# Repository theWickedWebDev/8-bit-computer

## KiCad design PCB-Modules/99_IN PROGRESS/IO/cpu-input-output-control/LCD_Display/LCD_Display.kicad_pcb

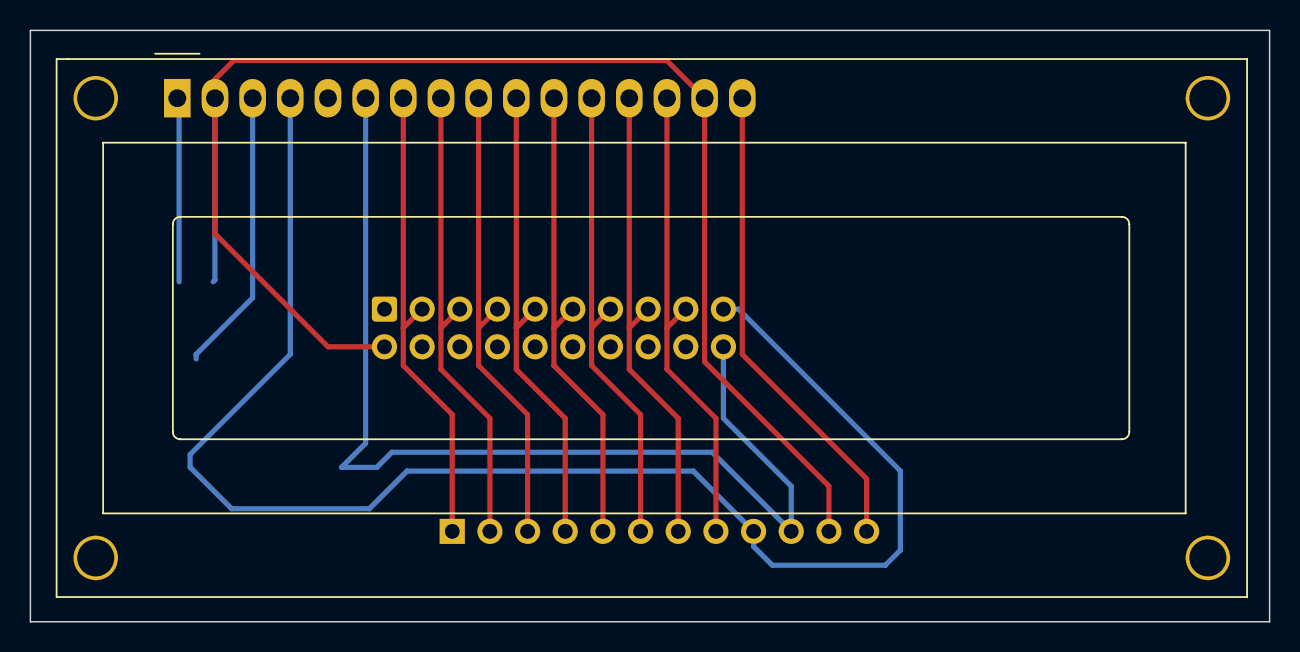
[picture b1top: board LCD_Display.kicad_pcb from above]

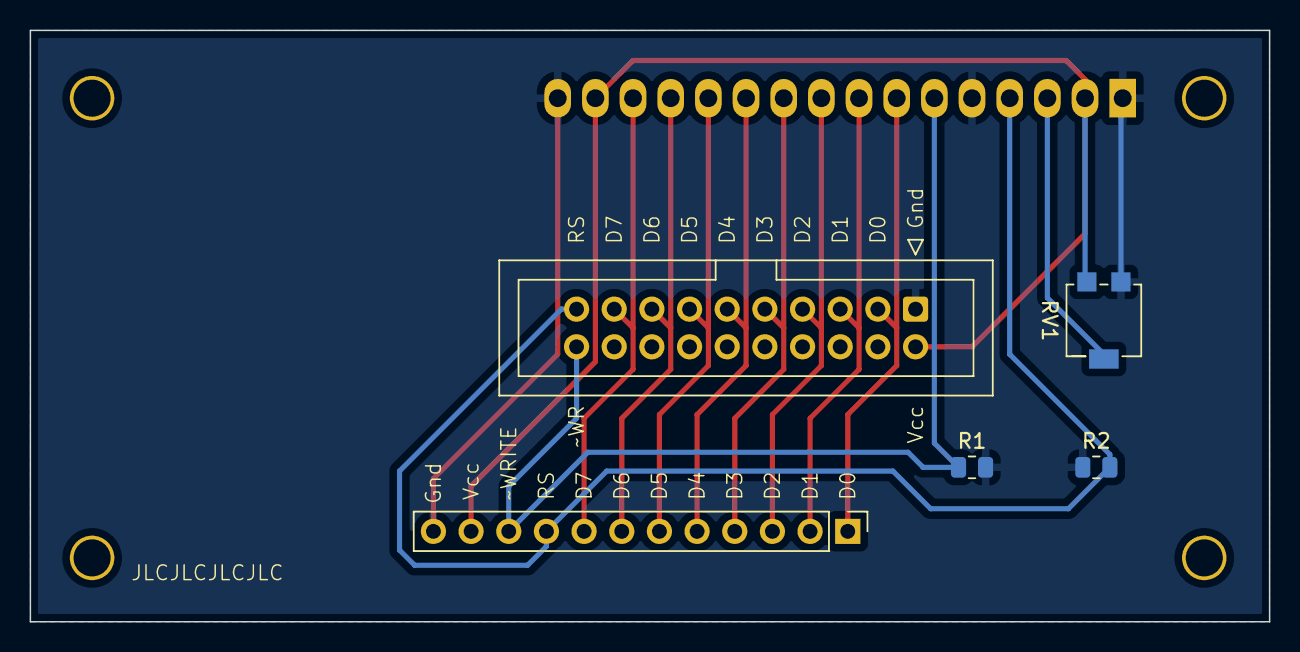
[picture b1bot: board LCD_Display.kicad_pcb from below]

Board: 2 copper layers, 83.6 x 39.9 mm, 6 parts (5 on the bottom side), 13 nets.

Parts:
DS1: WC1602A
J1: Conn_01x12; PinHeader_1x12_P2.54mm_Vertical
J21: Conn_02x20_Odd_Even; IDC-Header_2x10_P2.54mm_Vertical
R1, R2: R_Small_US; R_0805_2012Metric
RV1: R_Potentiometer_Trim_US; Potentiometer_Bourns_3224G_Horizontal

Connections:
/CONTRAST: DS1.3 (VO), RV1.2
/D0: DS1.7 (D0), J1.1, J21.3
/D1: DS1.8 (D1), J1.2, J21.5
/D2: DS1.9 (D2), J1.3, J21.7
/D3: DS1.10 (D3), J1.4, J21.9
/D4: DS1.11 (D4), J1.5, J21.11
/D5: DS1.12 (D5), J1.6, J21.13
/D6: DS1.13 (D6), J1.7, J21.15
/D7: DS1.14 (D7), J1.8, J21.17
/RS: DS1.4 (RS), J1.9, J21.19, R2.1
/~WRITE: DS1.6 (E), J1.10, J21.20, R1.1
GND: DS1.1 (VSS), DS1.5 (R/W), DS1.16 (LED(-)), J1.12, J21.1, R1.2, R2.2, RV1.3
VCC: DS1.2 (VDD), DS1.15 (LED(+)), J1.11, J21.2, RV1.1

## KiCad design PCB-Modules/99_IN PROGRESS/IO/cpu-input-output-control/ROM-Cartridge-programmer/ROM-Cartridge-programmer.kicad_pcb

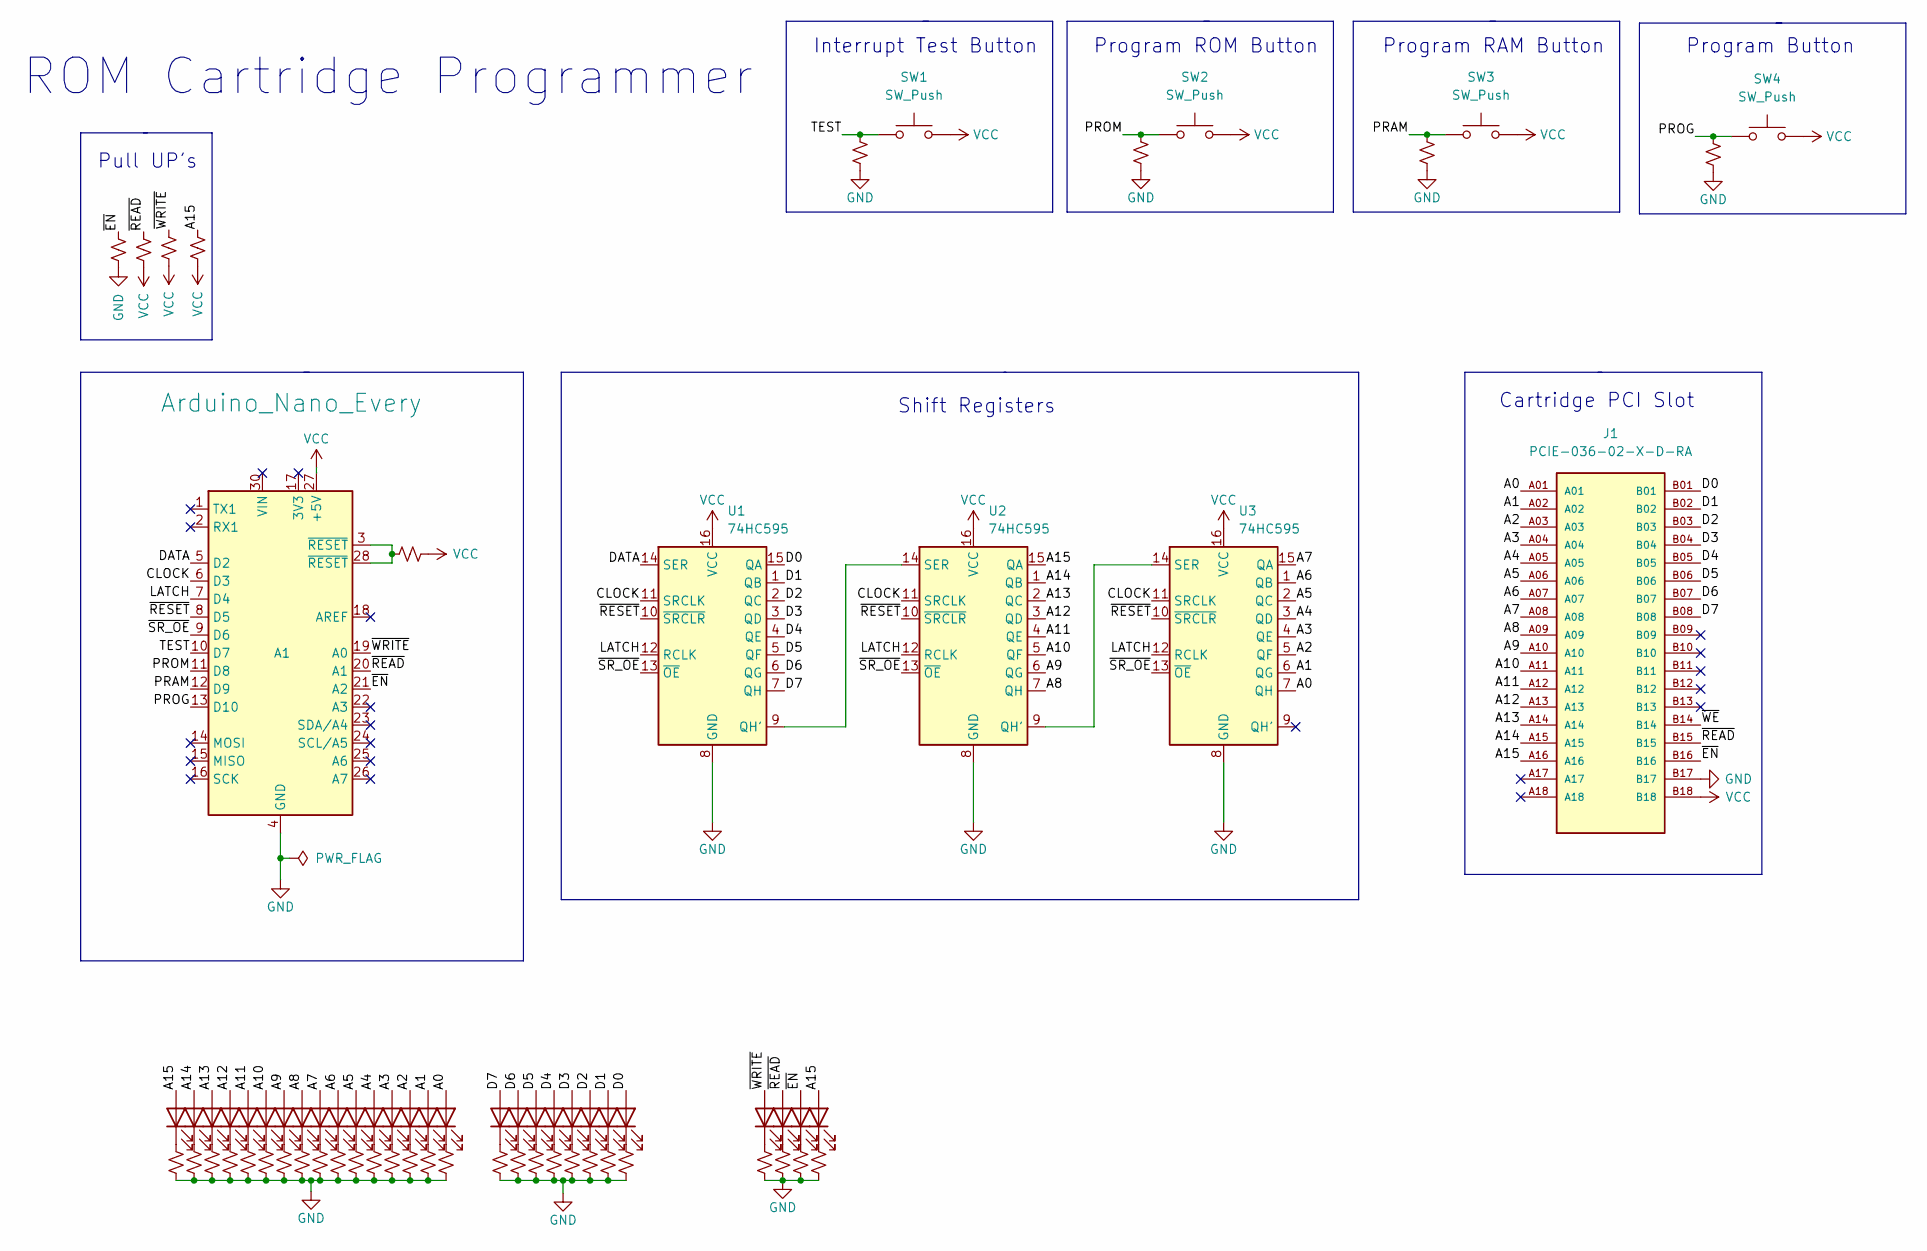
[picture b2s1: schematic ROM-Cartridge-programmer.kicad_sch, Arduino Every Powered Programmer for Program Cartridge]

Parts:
A1: Arduino_Nano_Every; Arduino_Nano
D1, D2, D3, D4, D5, D6, D7, D8, D9, D10, D11, D12, D13, D14, D15, D16, D17, D18, D19, D20, D21, D22, D23, D24, D25, D26, D27, D28: LED; LED_0805_2012Metric
J1: PCIE-036-02-X-D-RA; SAMTEC_PCIE-036-02-X-D-RA; PARTREV D
R1, R2, R3, R4, R5, R6, R7, R8, R9, R10, R11, R12, R13, R14, R15, R16, R17, R18, R19, R20, R21, R22, R23, R24, R25, R26, R27, R28, R29, R30, R31, R32, R33, R34, R35, R36, R37: R_Small_US; R_0805_2012Metric
SW1, SW2, SW3, SW4: SW_Push; SW_PUSH_6mm
U1, U2, U3: 74HC595; SOIC-16_3.9x9.9mm_P1.27mm

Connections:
/A0: D16.2 (A), J1.A01, U3.7 (QH)
/A1: D15.2 (A), J1.A02, U3.6 (QG)
/A2: D14.2 (A), J1.A03, U3.5 (QF)
/A3: D13.2 (A), J1.A04, U3.4 (QE)
/A4: D12.2 (A), J1.A05, U3.3 (QD)
/A5: D11.2 (A), J1.A06, U3.2 (QC)
/A6: D10.2 (A), J1.A07, U3.1 (QB)
/A7: D9.2 (A), J1.A08, U3.15 (QA)
/A8: D8.2 (A), J1.A09, U2.7 (QH)
/A9: D7.2 (A), J1.A10, U2.6 (QG)
/A10: D6.2 (A), J1.A11, U2.5 (QF)
/A11: D5.2 (A), J1.A12, U2.4 (QE)
/A12: D4.2 (A), J1.A13, U2.3 (QD)
/A13: D3.2 (A), J1.A14, U2.2 (QC)
/A14: D2.2 (A), J1.A15, U2.1 (QB)
/A15: D1.2 (A), D28.2 (A), J1.A16, R4.1, U2.15 (QA)
/CLOCK: A1.6 (D3), U1.11 (SRCLK), U2.11 (SRCLK), U3.11 (SRCLK)
/D0: D24.2 (A), J1.B01, U1.15 (QA)
/D1: D23.2 (A), J1.B02, U1.1 (QB)
/D2: D22.2 (A), J1.B03, U1.2 (QC)
/D3: D21.2 (A), J1.B04, U1.3 (QD)
/D4: D20.2 (A), J1.B05, U1.4 (QE)
/D5: D19.2 (A), J1.B06, U1.5 (QF)
/D6: D18.2 (A), J1.B07, U1.6 (QG)
/D7: D17.2 (A), J1.B08, U1.7 (QH)
/DATA: A1.5 (D2), U1.14 (SER)
/LATCH: A1.7 (D4), U1.12 (RCLK), U2.12 (RCLK), U3.12 (RCLK)
/PRAM: A1.12 (D9), R8.2, SW3.1
/PROG: A1.13 (D10), R9.2, SW4.1
/PROM: A1.11 (D8), R7.2, SW2.1
/TEST: A1.10 (D7), R6.2, SW1.1
/~EN: A1.21 (A2), D27.2 (A), J1.B16, R1.1
/~READ: A1.20 (A1), D26.2 (A), J1.B15, R2.1
/~RESET: A1.8 (D5), U1.10 (~SRCLR), U2.10 (~SRCLR), U3.10 (~SRCLR)
/~SR_OE: A1.9 (D6), U1.13 (~OE), U2.13 (~OE), U3.13 (~OE)
/~WE: J1.B14
/~WRITE: A1.19 (A0), D25.2 (A), R3.1
GND: A1.4 (GND), A1.29 (GND), J1.B17, R1.2, R6.1, R7.1, R8.1, R9.1, R10.1, R11.1, R12.1, R13.1, R14.1, R15.1, R16.1, R17.1, R18.1, R19.1, R20.1, R21.1, R22.1, R23.1, R24.1, R25.1, R26.1, R27.1, R28.1, R29.1, R30.1, R31.1, R32.1, R33.1, R34.1, R35.1, R36.1, R37.1, U1.8 (GND), U2.8 (GND), U3.8 (GND)
unnamed: A1.3 (~RESET), A1.28 (~RESET), R5.1
unnamed: D1.1 (K), R10.2
unnamed: D2.1 (K), R11.2
unnamed: D3.1 (K), R12.2
unnamed: D4.1 (K), R13.2
unnamed: D5.1 (K), R14.2
unnamed: D6.1 (K), R15.2
unnamed: D7.1 (K), R16.2
unnamed: D8.1 (K), R17.2
unnamed: D9.1 (K), R18.2
unnamed: D10.1 (K), R19.2
unnamed: D11.1 (K), R20.2
unnamed: D12.1 (K), R21.2
unnamed: D13.1 (K), R22.2
unnamed: D14.1 (K), R23.2
unnamed: D15.1 (K), R24.2
unnamed: D16.1 (K), R25.2
unnamed: D17.1 (K), R26.2
unnamed: D18.1 (K), R27.2
unnamed: D19.1 (K), R28.2
unnamed: D20.1 (K), R29.2
unnamed: D21.1 (K), R30.2
unnamed: D22.1 (K), R31.2
unnamed: D23.1 (K), R32.2
unnamed: D24.1 (K), R33.2
unnamed: D25.1 (K), R34.2
unnamed: D26.1 (K), R35.2
unnamed: D27.1 (K), R36.2
unnamed: D28.1 (K), R37.2
unnamed: U2.9 (QH'), U3.14 (SER)
unnamed: U1.9 (QH'), U2.14 (SER)
VCC: A1.27 (+5V), J1.B18, R2.2, R3.2, R4.2, R5.2, SW1.2, SW2.2, SW3.2, SW4.2, U1.16 (VCC), U2.16 (VCC), U3.16 (VCC)

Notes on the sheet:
Program ROM Button
Shift Registers
Cartridge PCI Slot
Interrupt Test Button
Program Button
Pull UP's
ROM Cartridge Programmer
Program RAM Button

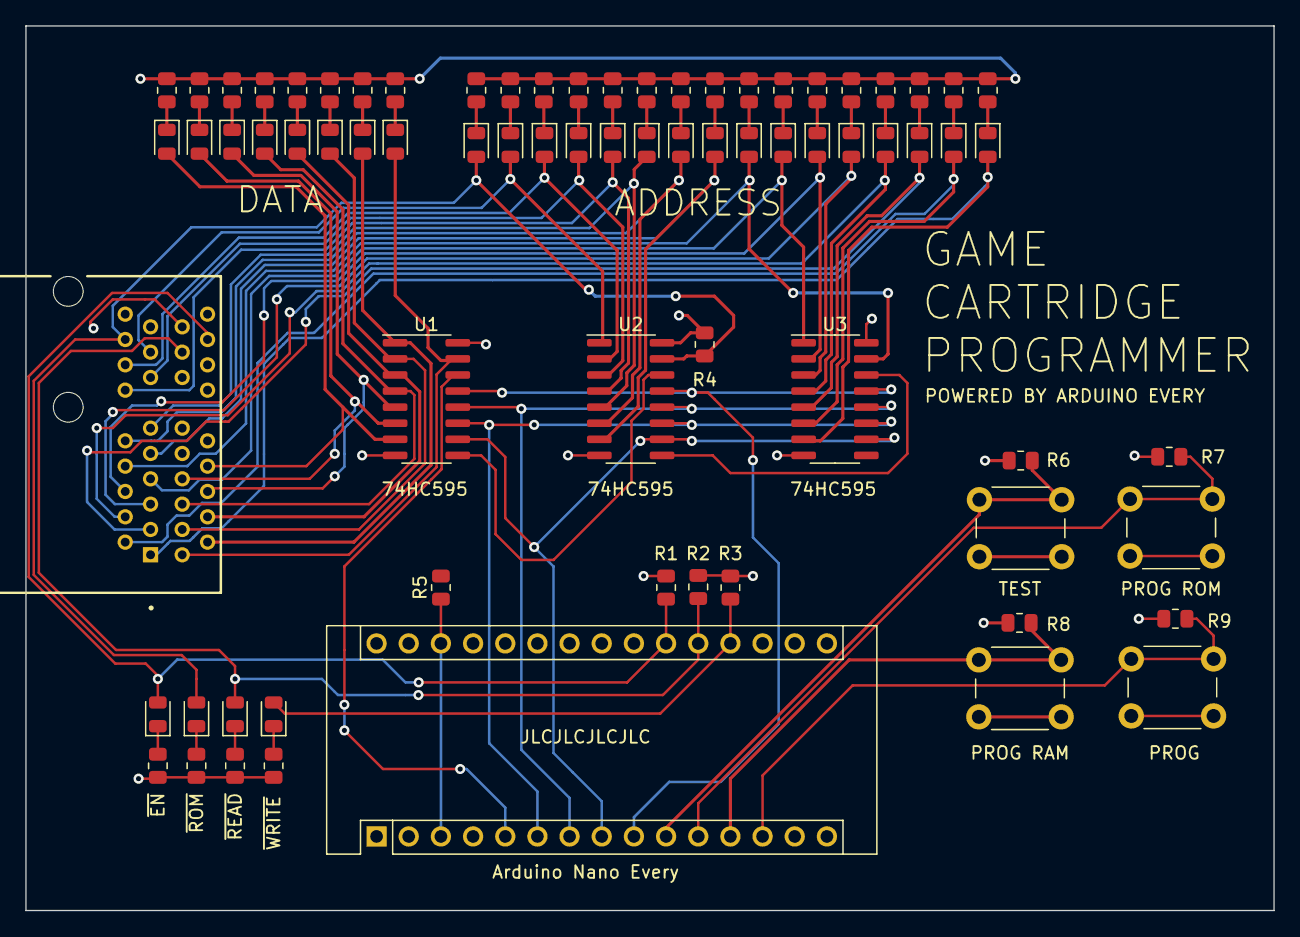
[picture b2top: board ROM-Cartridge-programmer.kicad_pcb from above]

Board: 4 copper layers, 98.6 x 69.8 mm, 74 parts (0 on the bottom side), 69 nets.

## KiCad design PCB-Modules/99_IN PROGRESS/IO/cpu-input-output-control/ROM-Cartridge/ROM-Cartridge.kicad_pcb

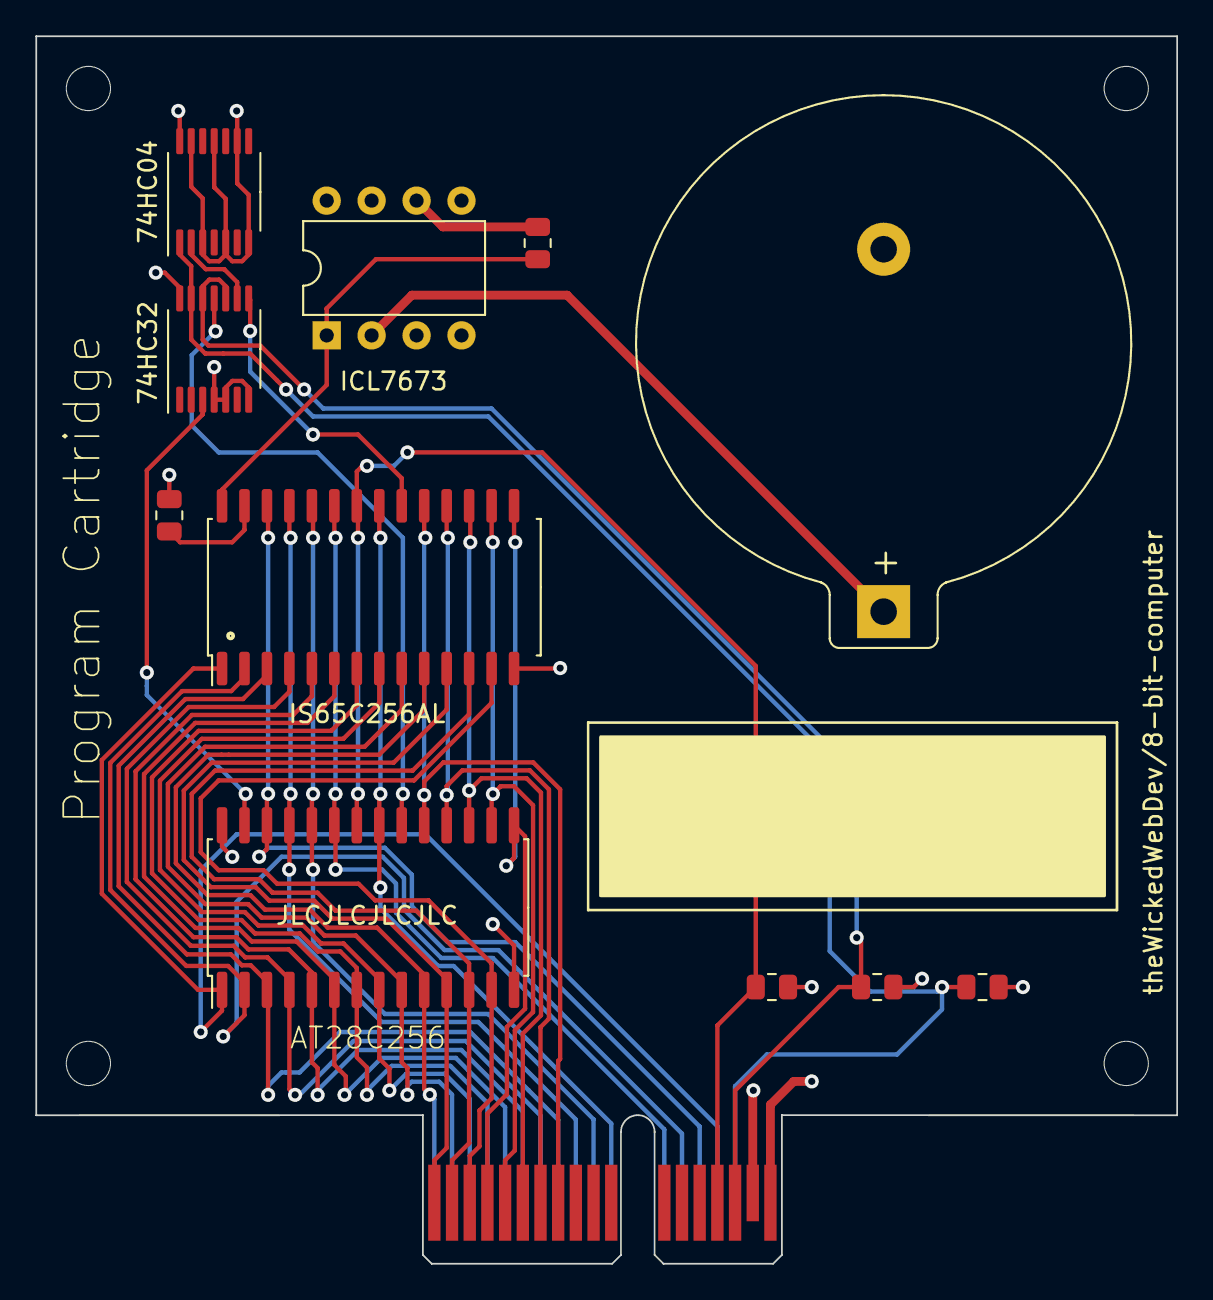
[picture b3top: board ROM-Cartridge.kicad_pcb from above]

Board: 4 copper layers, 64.5 x 69.4 mm, 12 parts (0 on the bottom side), 36 nets.

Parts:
BT1: Battery_Cell; BatteryHolder_Keystone_105_1x2430
R1, R2, R3, R4, R5: R_Small_US; R_0805_2012Metric
U1: 28C256; SOIC-28W_7.5x17.9mm_P1.27mm
U2: PCI; BUS_PCIexpress_x1
U3: ICL7673; DIP-8_W7.62mm
U4: 74LS04; TSSOP-14_4.4x5mm_P0.65mm
U5: IS65C256AL; SOP-28-RAM-ic
U6: 74LS32; TSSOP-14_4.4x5mm_P0.65mm

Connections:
/A0: U1.10 (A0), U2.A1 (Pin_1), U5.10 (A0)
/A1: U1.9 (A1), U2.A2 (Pin_2), U5.9 (A1)
/A2: U1.8 (A2), U2.A3 (Pin_3), U5.8 (A2)
/A3: U1.7 (A3), U2.A4 (Pin_4), U5.7 (A3)
/A4: U1.6 (A4), U2.A5 (Pin_5), U5.6 (A4)
/A5: U1.5 (A5), U2.A6 (Pin_6), U5.5 (A5)
/A6: U1.4 (A6), U2.A7 (Pin_7), U5.4 (A6)
/A7: U1.3 (A7), U2.A8 (Pin_8), U5.3 (A7)
/A8: U1.25 (A8), U2.A9 (Pin_9), U5.25 (A8)
/A9: U1.24 (A9), U2.A10 (Pin_10), U5.24 (A9)
/A10: U1.21 (A10), U2.A11 (Pin_11), U5.21 (A10)
/A11: U1.23 (A11), U2.A12 (Pin_12), U5.23 (A11)
/A12: U1.2 (A12), U2.A13 (Pin_13), U5.2 (A12)
/A13: U1.26 (A13), U2.A14 (Pin_14), U5.26 (A13)
/A14: U1.1 (A14), U2.A15 (Pin_15), U5.1 (A14)
/A15: R4.1, U2.A16 (Pin_16), U4.1, U6.13
/D0: U1.11 (D0), U2.B1 (Pin_17), U5.11 (D0)
/D1: U1.12 (D1), U2.B2 (Pin_18), U5.12 (D1)
/D2: U1.13 (D2), U2.B3 (Pin_19), U5.13 (D2)
/D3: U1.15 (D3), U2.B4 (Pin_20), U5.15 (D3)
/D4: U1.16 (D4), U2.B5 (Pin_21), U5.16 (D4)
/D5: U1.17 (D5), U2.B6 (Pin_22), U5.17 (D5)
/D6: U1.18 (D6), U2.B7 (Pin_23), U5.18 (D6)
/D7: U1.19 (D7), U2.B8 (Pin_24), U5.19 (D7)
/~EN: R1.1, U2.B16 (Pin_32), U6.10, U6.12
/~READ: R2.1, U1.22 (~OE), U2.B15 (Pin_31), U5.22 (~OE)
/~ROM_WRITE: U1.27 (~WE), U6.3
/~WRITE: R3.1, U5.27 (~WE)
GND: BT1.2 (-), R1.2, U1.14 (GND), U2.B17 (Pin_33), U3.4 (Gnd), U4.3, U4.5, U4.7 (GND), U4.9, U4.11, U4.13, U5.14 (GND), U6.4, U6.5, U6.7 (GND)
unnamed: BT1.1 (+), U3.2 (Vs)
unnamed: R5.2, U3.6 (PBar)
unnamed: U4.2, U6.9
RAM_POWER: R5.1, U3.1 (VO), U5.28 (VCC)
RAM_SELECT: U5.20 (~CS), U6.8
ROM_SELECT: U1.20 (~CS), U6.11
VCC: R2.2, R3.2, R4.2, U1.28 (VCC), U2.B18 (Pin_34), U3.8 (Vp), U4.14 (VCC), U6.14 (VCC)

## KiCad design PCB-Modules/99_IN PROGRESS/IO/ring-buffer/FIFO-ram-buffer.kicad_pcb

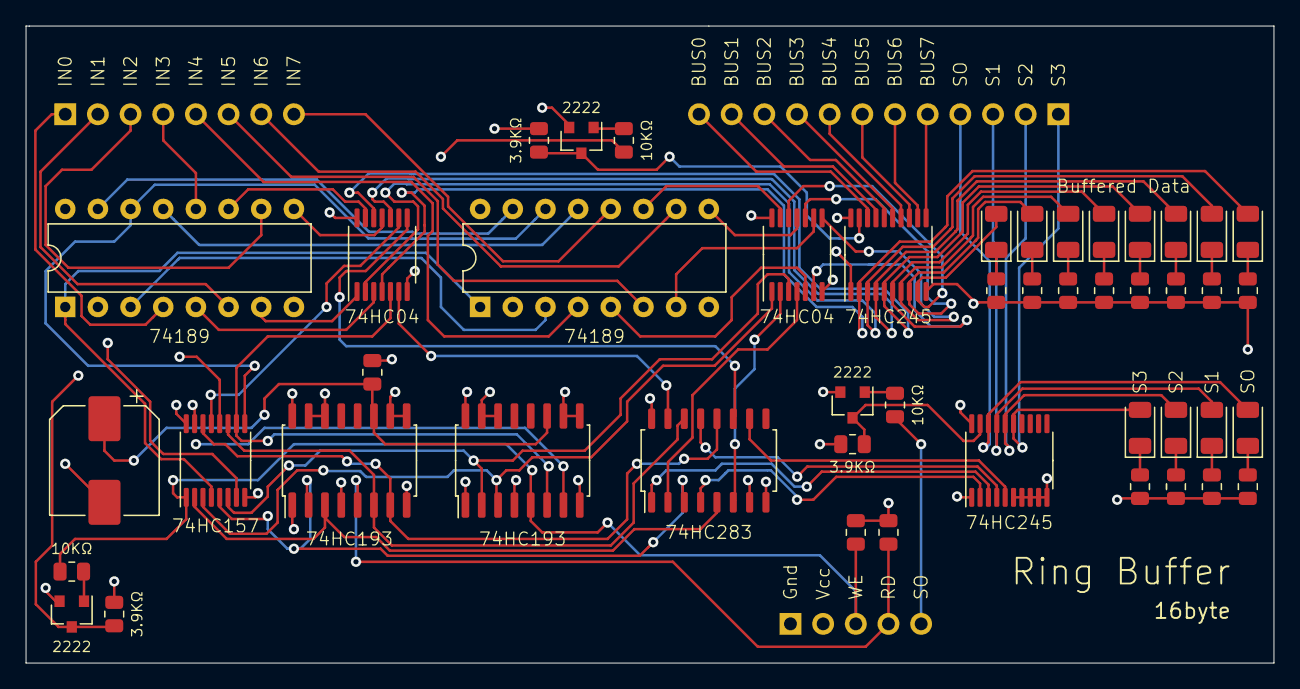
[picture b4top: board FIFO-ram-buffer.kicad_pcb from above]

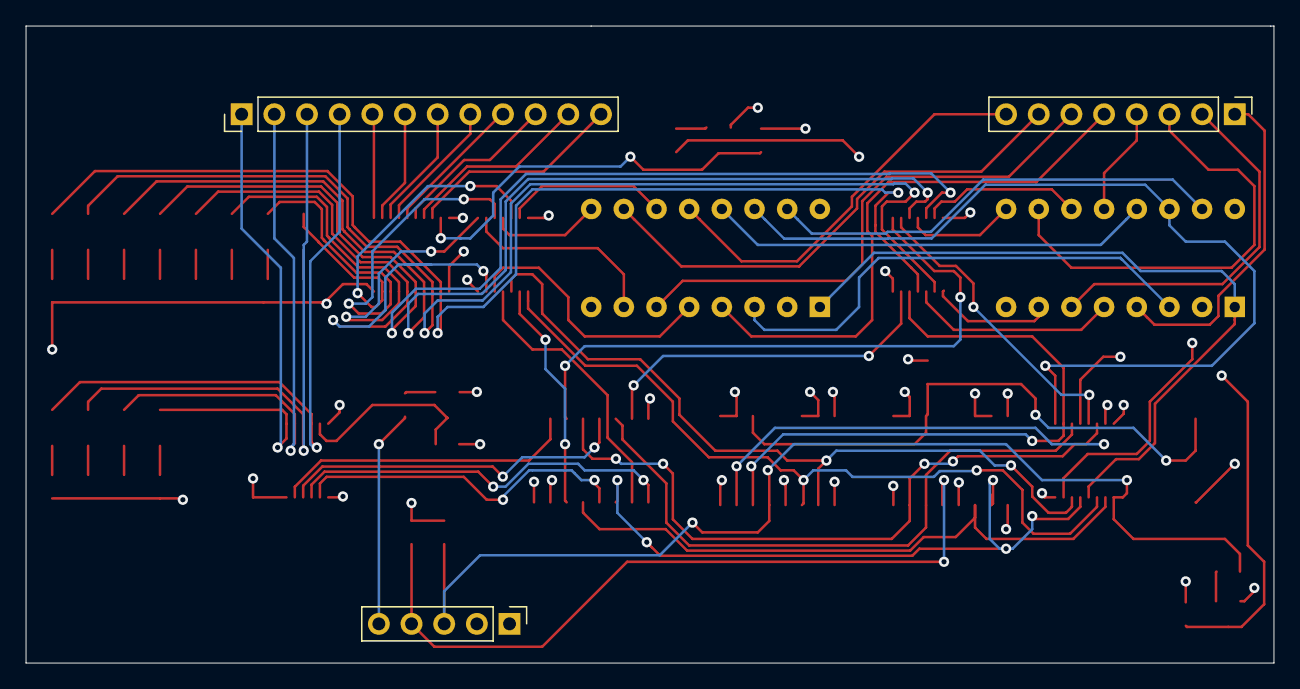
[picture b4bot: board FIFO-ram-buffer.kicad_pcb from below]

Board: 4 copper layers, 97.0 x 49.5 mm, 50 parts (3 on the bottom side), 80 nets.

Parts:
C1: C; CP_Elec_8x10
D1, D2, D3, D4, D5, D6, D7, D8, D9, D10, D11, D12: LED; LED_1206_3216Metric
J1: Conn_01x05; PinHeader_1x05_P2.54mm_Vertical
J2: Conn_01x08; PinHeader_1x08_P2.54mm_Vertical
J3: Conn_01x12; PinHeader_1x12_P2.54mm_Vertical
Q1, Q2, Q3: PMBT2222; SOT-23
R1, R6, R7: 10kohm; R_0805_2012Metric
R2, R8, R9: 3.9kohm; R_0805_2012Metric
R3, R4, R5, R10, R11, R12, R13, R14, R15, R16, R17, R18, R19, R20, R21: 1kohm; R_0805_2012Metric
U1, U2: 74LS04; TSSOP-14_4.4x5mm_P0.65mm
U3: 74HC157PW,118; TSSOP-16_4.4x5mm_P0.65mm
U4, U6: 74LS193; SO-16_5.3x10.2mm_P1.27mm
U5, U7: 74189; DIP-16_W7.62mm
U8: 74LS283; SOIC-16_4.55x10.3mm_P1.27mm
U9, U10: 74HC245; TSSOP-20_4.4x6.5mm_P0.65mm

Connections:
BUS0: J3.12, U10.18
BUS1: J3.11, U10.17
BUS2: J3.10, U10.16
BUS3: J3.9, U10.15
BUS4: J3.8, U10.14
BUS5: J3.7, U10.13
BUS6: J3.6, U10.12
BUS7: J3.5, U10.11
DATACOUNT0: U8.4, U9.2
DATACOUNT1: U8.1, U9.3
DATACOUNT2: U8.13, U9.4
DATACOUNT3: U8.10, U9.5
GND: C1.2, J1.1, Q1.2, Q2.2, Q3.2, R3.2, R4.2, R10.2, R11.2, R12.2, R13.2, R14.2, R15.2, R16.2, R17.2, R18.2, R19.2, R20.2, R21.2, U1.7, U2.7, U3.8, U3.15, U4.1, U4.8, U4.9, U4.10, U4.14, U4.15, U5.2, U5.8, U6.1, U6.8, U6.9, U6.10, U6.14, U6.15, U7.2, U7.8, U8.8, U9.6, U9.7, U9.8, U9.9, U9.10, U10.10
INPUT0: J2.1, U5.4
INPUT1: J2.2, U5.6
INPUT2: J2.3, U5.10
INPUT3: J2.4, U5.12
INPUT4: J2.5, U7.4
INPUT5: J2.6, U7.6
INPUT6: J2.7, U7.10
INPUT7: J2.8, U7.12
unnamed: C1.1, R5.2, U4.11, U6.11
unnamed: D1.1, R10.1
unnamed: D2.1, R11.1
unnamed: D3.1, R12.1
unnamed: D4.1, R13.1
unnamed: D5.1, R14.1
unnamed: D6.1, R15.1
unnamed: D7.1, R16.1
unnamed: D8.1, R17.1
unnamed: D9.1, R18.1
unnamed: D10.1, R19.1
unnamed: D11.1, R20.1
unnamed: D12.1, R21.1
unnamed: Q1.1, R1.2
unnamed: Q2.1, R6.2
unnamed: Q2.3, R8.1, U9.19
unnamed: Q3.1, R7.2
unnamed: Q3.3, R9.1, U10.19
unnamed: U1.1, U5.7
unnamed: U1.3, U5.5
unnamed: U1.6, U8.15
unnamed: U1.8, U8.11
unnamed: U1.11, U5.9
unnamed: U1.13, U5.11
unnamed: U2.2, U8.6
unnamed: U2.4, U8.2
unnamed: U2.5, U7.5
unnamed: U2.9, U7.7
unnamed: U2.11, U7.9
unnamed: U2.13, U7.11
unnamed: U3.4, U5.1, U7.1
unnamed: U3.7, U5.15, U7.15
unnamed: U3.9, U5.14, U7.14
unnamed: U3.12, U5.13, U7.13
OUTPUT_STATUS: J1.5, R6.1
R0: U3.2, U4.3, U8.5
R1: U3.5, U4.2, U8.3
R2: U3.11, U4.6, U8.14
R3: U3.14, U4.7, U8.12
RAM0: D12.2, U1.4, U10.2
RAM1: D11.2, U1.2, U10.3
RAM2: D10.2, U1.10, U10.4
RAM3: D9.2, U1.12, U10.5
RAM4: D8.2, U2.6, U10.6
RAM5: D7.2, U2.8, U10.7
RAM6: D5.2, U2.10, U10.8
RAM7: D3.2, U2.12, U10.9
READ: J1.4, R3.1, R7.1, U4.5
STATUS0: D1.2, J3.4, U9.18
STATUS1: D2.2, J3.3, U9.17
STATUS2: D4.2, J3.2, U9.16
STATUS3: D6.2, J3.1, U9.15
VCC: J1.2, R2.2, R5.1, R8.2, R9.2, U1.14, U2.14, U3.16, U4.4, U4.16, U5.16, U6.4, U6.16, U7.16, U8.7, U8.16, U9.1, U9.20, U10.1, U10.20
W0: U2.1, U3.3, U6.3
W1: U2.3, U3.6, U6.2
W2: U1.5, U3.10, U6.6
W3: U1.9, U3.13, U6.7
WRITE: J1.3, R1.1, R4.1, U3.1, U6.5
~WE: Q1.3, R2.1, U5.3, U7.3

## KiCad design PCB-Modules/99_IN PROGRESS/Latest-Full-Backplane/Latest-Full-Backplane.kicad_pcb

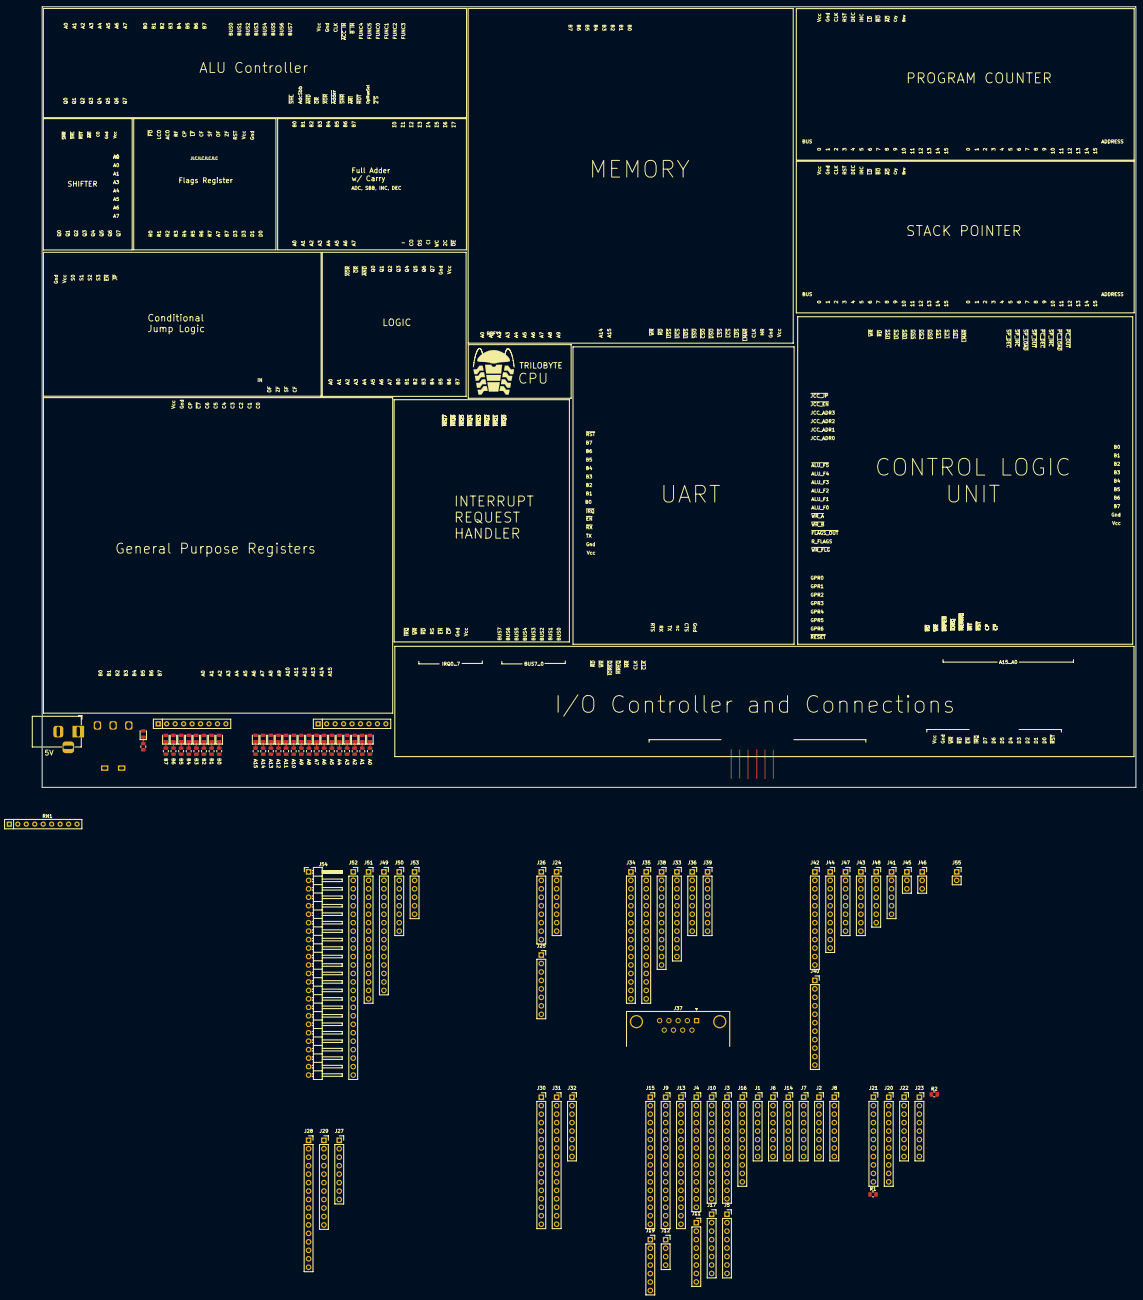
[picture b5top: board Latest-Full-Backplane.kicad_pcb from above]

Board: 2 copper layers, 328.1 x 234.2 mm, 111 parts (0 on the bottom side), 160 nets.

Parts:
D1, D2, D3, D4, D5, D6, D7, D8, D9, D10, D11, D12, D13, D14, D15, D16, D17, D18, D19, D20, D21, D22, D23, D24, D25: LED; LED_0805_2012Metric
J1, J2, J5, J6, J7, J8, J11, J14, J17, J22, J23, J24, J25, J27, J32, J36, J39, J43, J47, J50: Conn_01x08; PinSocket_1x08_P2.54mm_Vertical
J3, J10: Conn_01x13; PinSocket_1x13_P2.54mm_Vertical
J4: Conn_01x14; PinSocket_1x14_P2.54mm_Vertical
J9, J13, J15, J28, J30, J31, J34, J35, J51: Conn_01x16; PinSocket_1x16_P2.54mm_Vertical
J12: Conn_01x04; PinSocket_1x04_P2.54mm_Vertical
J16, J21, J29, J33, J40: Conn_01x11; PinSocket_1x11_P2.54mm_Vertical
J18: Barrel_Jack_MountingPin; BarrelJack_Horizontal
J19, J48: Conn_01x07; PinSocket_1x07_P2.54mm_Vertical
J20: Conn_01x12; PinSocket_1x11_P2.54mm_Vertical
J26: Conn_01x09; PinSocket_1x09_P2.54mm_Vertical
J37: Conn_01x09; DSUB-9_Female_Horizontal_P2.77x2.84mm_EdgePinOffset4.94mm_H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
J38, J42: Conn_01x12; PinSocket_1x12_P2.54mm_Vertical
J41, J53: Conn_01x06; PinSocket_1x06_P2.54mm_Vertical
J44: Conn_01x10; PinSocket_1x10_P2.54mm_Vertical
J45, J46: Conn_01x03; PinSocket_1x03_P2.54mm_Vertical
J49: Conn_01x15; PinSocket_1x15_P2.54mm_Vertical
J52: Conn_01x25; PinSocket_1x25_P2.54mm_Vertical
J54: Conn_01x25; PinHeader_1x25_P2.54mm_Horizontal
J55: Conn_01x02; PinSocket_1x02_P2.54mm_Vertical
R1, R2, R3, R4, R5, R6, R7, R8, R9, R10, R11, R12, R13, R14, R15, R16, R17, R18, R19, R20, R21, R22, R23, R24, R25, R26, R27: R_US; R_0805_2012Metric
RN1, RN2, RN3: R_Network08; R_Array_SIP9
SW1: SW_DPDT_x2; 100SP1T1B4M6RE

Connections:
/ADDR0: J20.1, J23.1, J29.1, J43.1
/ADDR1: J20.2, J23.2, J29.2, J43.2
/ADDR2: J20.3, J23.3, J29.3, J43.3
/ADDR3: J20.4, J23.4, J29.4, J43.4
/ADDR4: J20.5, J23.5, J29.5, J30.4, J43.5
/ADDR5: J20.6, J23.6, J29.6, J43.6
/ADDR6: J20.7, J23.7, J29.7, J43.7
/ADDR7: J20.8, J23.8, J26.9, J29.8, J43.8
/ADDR8: J20.9, J26.8, J29.9
/ADDR9: J20.10, J26.7, J29.10
/ADDR10: J20.11, J26.6, J29.11
/ALU/ALU_A0: J17.1, J18.1, J19.1
/ALU/ALU_A1: J17.2, J18.2, J19.2
/ALU/ALU_A2: J17.3, J18.3, J19.3
/ALU/ALU_A3: J17.4, J19.4
/ALU/ALU_A4: J17.5, J19.5
/ALU/ALU_A5: J16.11, J17.6, J19.6
/ALU/ALU_A6: J16.10, J17.7, J19.7
/ALU/ALU_A7: J6.6, J16.9, J17.8
/ALU/ALU_B0: J14.1, J15.1, J16.8
/ALU/ALU_B1: J14.2, J15.2, J16.7
/ALU/ALU_B2: J14.3, J15.3, J16.6
/ALU/ALU_B3: J14.4, J15.4, J16.5
/ALU/ALU_B4: J14.5, J15.5, J16.4
/ALU/ALU_B5: J14.6, J15.6, J16.3
/ALU/ALU_B6: J14.7, J15.7, J16.2
/ALU/ALU_B7: J6.5, J14.8, J15.8, J16.1
/ALU/ALU_FUNC_0: J2.4, J36.6
/ALU/ALU_FUNC_1: J2.3, J36.7
/ALU/ALU_FUNC_2: J2.2, J36.8
/ALU/ALU_Q0: J10.4, J11.8, J13.8
/ALU/ALU_Q1: J10.5, J11.7, J13.7
/ALU/ALU_Q2: J10.6, J11.6, J13.6
/ALU/ALU_Q3: J10.7, J11.5, J13.5
/ALU/ALU_Q4: J10.8, J11.4, J12.4, J13.4
/ALU/ALU_Q5: J10.9, J11.3, J12.3, J13.3
/ALU/ALU_Q6: J6.8, J10.10, J11.2, J12.2, J13.2
/ALU/ALU_Q7: J6.7, J10.11, J11.1, J12.1, J13.1
/ALU/CF: J1.7, J4.4, J7.4
/ALU/CLOCK: J21.9, J24.4, J30.6, J34.2, J40.5
/ALU/JCC_ADR0: J3.6, J37.1
/ALU/JCC_ADR1: J3.5, J37.3
/ALU/JCC_ADR2: J3.4, J37.2
/ALU/JCC_ADR3: J3.3, J37.4
/ALU/OF: J1.5, J4.1
/ALU/SF: J1.6, J4.3
/ALU/ZF: J1.4, J4.2
/ALU/~JCC_EN: J3.2, J37.5
/ALU/~JCC_LD_PC_COND: J3.1, J37.6
/ALU/~LATCH_A: J2.8, J36.5
/ALU/~LATCH_B: J2.7, J36.4
/ALU/~LATCH_FLAGS: J1.8, J36.1
/BUS0: J6.1, J9.1, J25.8, J28.1, J31.8, J33.1, J45.2, J51.2
/BUS1: J6.2, J9.2, J25.7, J28.2, J31.7, J33.2, J45.3, J51.3
/BUS2: J6.3, J9.3, J25.6, J28.3, J31.6, J33.3, J41.6, J51.4
/BUS3: J6.4, J9.4, J25.5, J28.4, J31.5, J33.4, J41.5, J51.5
/BUS4: J9.5, J25.4, J28.5, J31.4, J33.5, J41.4, J51.6
/BUS5: J9.6, J25.3, J28.6, J31.3, J33.6, J41.3, J51.7
/BUS6: J9.7, J25.2, J28.7, J31.2, J33.7, J41.2, J51.8
/BUS7: J9.8, J25.1, J28.8, J31.1, J33.8, J41.1, J51.9
/Control Unit/GPR0: J27.1, J35.8
/Control Unit/GPR1: J27.2, J35.7
/Control Unit/GPR2: J27.3, J35.6
/Control Unit/GPR3: J27.4, J35.5
/Control Unit/GPR4: J27.5, J35.4
/Control Unit/GPR5: J27.6, J35.3
/Control Unit/GPR6: J27.7, J35.2
/Control Unit/~CLOCK: J34.1, J40.6
/Control Unit/~CPU_INTERRUPT: J30.1, J34.4
/Control Unit/~IO_REQUEST: J34.5, J40.3
/Control Unit/~IRQ_MASK_PORT_EN: J30.5, J34.6
/Control Unit/~LATCH_CODE_SEGMENT: J24.7, J38.3
/Control Unit/~LATCH_DATA_SEGMENT: J24.6, J38.2
/Control Unit/~LATCH_MAR: J24.5, J38.1
/Control Unit/~LATCH_STACK_SEGMENT: J24.8, J38.4
/Control Unit/~PC_BUS_OUT: J21.4, J39.1
/Control Unit/~PC_DEC: J22.7, J39.4
/Control Unit/~PC_INC: J22.6, J39.3
/Control Unit/~PC_LOAD: J21.5, J39.2
/Control Unit/~READ: J30.3, J34.8, J40.1, J44.3, J51.12
/Control Unit/~RESET: J34.3, J35.1
/Control Unit/~SP_BUS_OUT: J22.4, J39.5
/Control Unit/~SP_DEC: J21.7, J39.8
/Control Unit/~SP_INC: J21.6, J39.7
/Control Unit/~SP_LOAD: J22.5, J39.6
/Control Unit/~WRITE: J30.2, J34.7, J40.2, J44.4, J51.13
/GPR/~GPR7: J21.8, J22.8, J24.3, J27.8, J40.4, J45.1, J51.1
/Stack Pointer/~PC_ADDR_OUT: J21.3, R1.2
/Stack Pointer/~SP_ADDR_OUT: J22.3, R2.2
ADC_SBB: J5.2, J7.3
ADDER_OUT: J5.6, J7.1
ADDR0: D16.2 (A), RN2.9 (R8)
ADDR1: D15.2 (A), RN2.8 (R7)
ADDR2: D14.2 (A), RN2.7 (R6)
ADDR3: D13.2 (A), RN2.6 (R5)
ADDR4: D12.2 (A), RN2.5 (R4)
ADDR5: D11.2 (A), RN2.4 (R3)
ADDR6: D10.2 (A), RN2.3 (R2)
ADDR7: D9.2 (A), RN2.2 (R1)
ADDR8: D8.2 (A), RN1.9 (R8)
ADDR9: D7.2 (A), RN1.8 (R7)
ADDR10: D6.2 (A), RN1.7 (R6)
ADDR11: D5.2 (A), RN1.6 (R5)
ADDR12: D4.2 (A), RN1.5 (R4)
ADDR13: D3.2 (A), RN1.4 (R3)
ADDR14: D2.2 (A), RN1.3 (R2)
ADDR15: D1.2 (A), RN1.2 (R1)
BUS0: D25.2 (A), RN3.9 (R8)
BUS1: D24.2 (A), RN3.8 (R7)
BUS2: D22.2 (A), RN3.7 (R6)
BUS3: D21.2 (A), RN3.6 (R5)
BUS4: D20.2 (A), RN3.5 (R4)
BUS5: D19.2 (A), RN3.4 (R3)
BUS6: D18.2 (A), RN3.3 (R2)
BUS7: D17.2 (A), RN3.2 (R1)
GND: J1.1, J1.3, J3.8, J7.7, J8.6, J10.12, J21.10, J24.2, J30.7, J33.9, J44.2, J51.14, J52.5, J53.6, J54.6, J55.2, R1.1, R2.1, R3.2, R4.2, R5.2, R6.2, R7.2, R8.2, R9.2, R10.2, R11.2, R12.2, R13.2, R14.2, R15.2, R16.2, R17.2, R18.2, R19.2, R20.2, R21.2, R22.2, R23.2, R24.2, R25.2, R26.2, R27.2, RN1.1 (common), RN2.1 (common), RN3.1 (common)
unnamed: D1.1 (K), R3.1
unnamed: D2.1 (K), R4.1
unnamed: D3.1 (K), R5.1
unnamed: D4.1 (K), R6.1
unnamed: D5.1 (K), R7.1
unnamed: D6.1 (K), R8.1
unnamed: D7.1 (K), R9.1
unnamed: D8.1 (K), R10.1
unnamed: D9.1 (K), R11.1
unnamed: D10.1 (K), R12.1
unnamed: D11.1 (K), R13.1
unnamed: D12.1 (K), R14.1
unnamed: D13.1 (K), R15.1
unnamed: D14.1 (K), R16.1
unnamed: D15.1 (K), R17.1
unnamed: D16.1 (K), R18.1
unnamed: D17.1 (K), R19.1
unnamed: D18.1 (K), R20.1
unnamed: D19.1 (K), R21.1
unnamed: D20.1 (K), R22.1
unnamed: D21.1 (K), R23.1
unnamed: D22.1 (K), R24.1
unnamed: D23.1 (K), R25.1
unnamed: D24.1 (K), R26.1
unnamed: D25.1 (K), R27.1
unnamed: J55.1, SW1.5 (B)
SER_CTS: J52.8, J53.5, J54.5
SER_RTS: J52.7, J53.1, J54.1
SER_RX: J52.2, J53.2, J54.2
SER_TX: J52.3, J53.3, J54.3
VCC: D23.2 (A), J1.2, J3.7, J7.8, J8.7, J10.13, J21.11, J24.1, J30.8, J33.10, J44.1, J51.15, SW1.4 (A)
~AND: J5.3, J10.3
~IRQ1: J32.7, J42.2, J48.7
~IRQ2: J32.6, J42.3, J48.6
~IRQ3: J32.5, J42.4, J48.5
~IRQ4: J32.4, J42.5, J48.4
~IRQ5: J32.3, J42.6, J48.3
~IRQ6: J32.2, J42.7, J48.2
~IRQ7: J32.1, J42.8, J48.1
~OR: J5.4, J10.2
~SHIFTER_ARI: J5.8, J8.4
~SHIFTER_SHL: J5.1, J8.2
~SHIFTER_SHR: J5.7, J8.1
~XOR: J5.5, J10.1
